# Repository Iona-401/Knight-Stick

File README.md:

# Knight-Stick 🕹️✈️

An open-source, fully 3D-printable flight stick engineered for high-precision simulation, modular assembly, and custom hardware integration.

---

## Overview

Commercial flight simulation gear is often prohibitively expensive or locked into closed ecosystems. **Knight-Stick** bridges that gap by providing a fully customizable, high-performance flight controller that you can manufacture at home using 3D printing and custom electronics.

Designed with a heavy focus on ergonomic feel, mechanical durability, and low-latency input processing, this project brings together mechanical CAD, PCB design, and embedded firmware.

---

## Key Features

* **Ergonomic & Modular CAD:** Designed for additive manufacturing, optimizing print orientation for strength and tactile comfort.
* **Precision Inputs:** Built around low-latency sensor architecture to ensure smooth, dead-zone-free axis tracking and crisp button actuation.
* **Custom Electronics:** Dedicated PCB layout for clean signal routing and reliable peripheral connections.
* **Open Source:** Complete hardware schematics, firmware source code, and STL/CAD files available for modification and community contribution.

---

## Repository Structure

```text
Knight-Stick/
├── cad/          # 3D printable models, mechanical assemblies, and STEP/STL files
├── hardware/     # Schematics, board layouts, and manufacturing files
├── firmware/     # Microcontroller source code and USB HID implementation
└── docs/         # Build guides, wiring diagrams, and assembly instructions

```

---

## Getting Started & Bill of Materials (BOM)

To build your own Knight-Stick, check out the documentation and release files in the respective directories:

1. **Hardware & Electronics:** Review the `hardware/` folder for schematic diagrams and PCB fabrication files.
2. **Mechanical Parts:** Grab the latest printable parts from the `cad/` folder. Ensure you follow recommended print settings for structural rigidity (e.g., adequate infill and wall counts).
3. **Firmware:** Flash the controller using the source code provided in the `firmware/` directory.

---

## Contributing

Contributions, feedback, and forks are always welcome! If you have ideas for improved gimbal geometry, alternative sensor integrations, or firmware enhancements, feel free to open an issue or submit a pull request.

---

## License

This project is open-source. See the repository for license details.

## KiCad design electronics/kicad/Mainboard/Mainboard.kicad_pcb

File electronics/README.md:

# Electronics

This directory contains the complete electronics design for the **Knight Stick**
flight stick, including the schematic, PCB layout, and manufacturing outputs.

The electronics are built around an **ESP32**, providing USB and/or wireless
capabilities suitable for use as a flight simulation controller or general
HID device.

## Contents

- `kicad/`  
  Source design files created with **KiCad**, including:
  - Schematics
  - PCB layout
  - Project configuration files  
  These files represent the authoritative source for the electronics design.

- `gerbers/`  
  Fabrication-ready Gerber and drill files, organized by hardware revision.
  These files can be used directly with PCB manufacturers.

- `bom/`  
  Bill of Materials (BOM) files listing all electronic components required to
  assemble the PCB.

## Manufacturing Notes

- Gerber files are provided for convenience; always refer to the KiCad source
  files if modifications are required.
- Check the BOM and schematic carefully before ordering or assembling boards.

## License

All electronics design files in this directory are licensed under the  
**CERN Open Hardware License v2 – Strongly Reciprocal (CERN-OHL-S)**.

See the root `LICENSE-hardware.txt` file for full license terms.

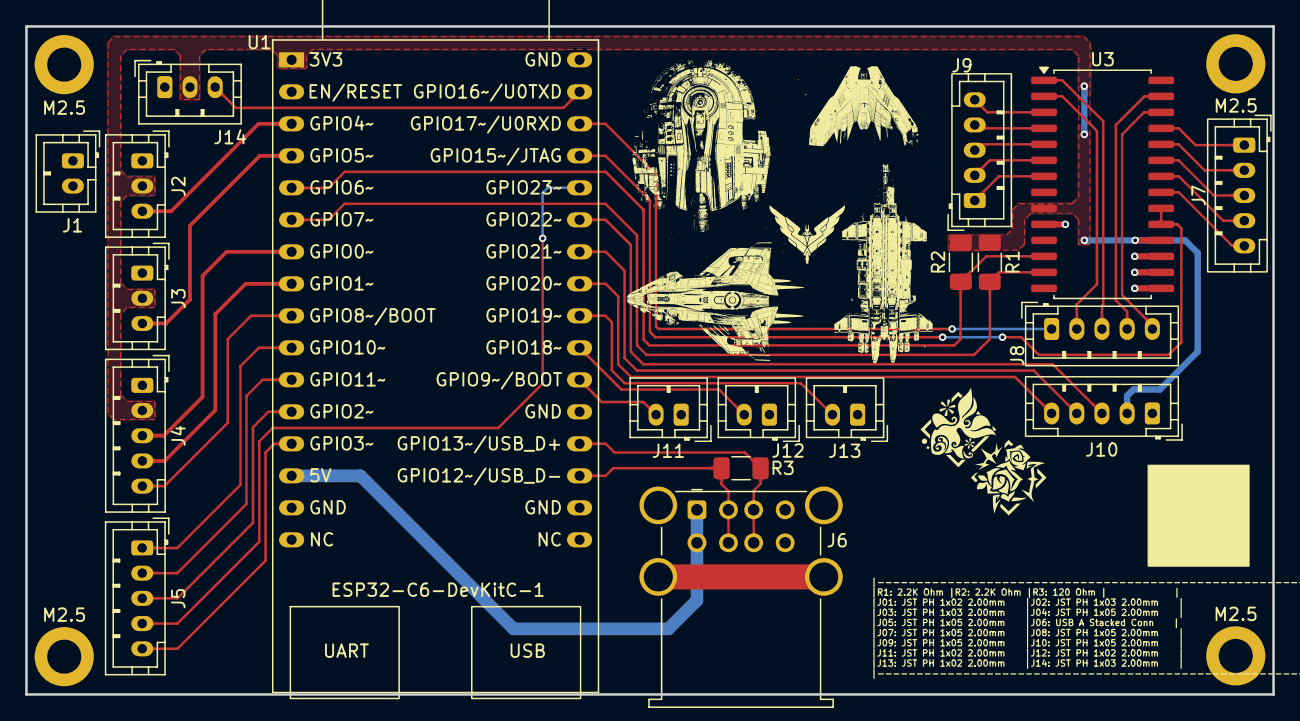
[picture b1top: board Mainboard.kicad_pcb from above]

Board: 2 copper layers, 99.0 x 53.0 mm, 23 parts (0 on the bottom side), 40 nets.

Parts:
J1: GND Pair; JST_PH_B2B-PH-K_1x02_P2.00mm_Vertical
J2: X-Axis Hall; JST_PH_B3B-PH-K_1x03_P2.00mm_Vertical
J3: Y-Axis Hall; JST_PH_B3B-PH-K_1x03_P2.00mm_Vertical
J4, J5, J7, J8, J9, J10: Conn_01x05; JST_PH_B5B-PH-K_1x05_P2.00mm_Vertical
J6: USB_A_Stacked; USB_A_Wuerth_61400826021_Horizontal_Stacked
J11: Box Switch 1; JST_PH_B2B-PH-K_1x02_P2.00mm_Vertical
J12: Box Switch 2; JST_PH_B2B-PH-K_1x02_P2.00mm_Vertical
J13: Bos Switch 3; JST_PH_B2B-PH-K_1x02_P2.00mm_Vertical
J14: LED Strip; JST_PH_B3B-PH-K_1x03_P2.00mm_Vertical
M2.5, M2.5#2, M2.5#3, M2.5#4: MountingHole_2.7mm_M2.5_DIN965_Pad
R1, R2: 2K2; R_1206_3216Metric_Pad1.30x1.75mm_HandSolder
R3: 120; R_1206_3216Metric_Pad1.30x1.75mm_HandSolder
U1: ESP32-C6-DevKitC-1
U3: MCP23017x-x-SO; SOIC-28W_7.5x17.9mm_P1.27mm

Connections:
3V3: J2.2, J3.2, J4.2, J10.2, J14.2, R1.1, R2.1, U1.1 (3V3), U3.9 (V_{DD}), U3.18 (~RESET)
5V: J6.1 (VBUS1), J6.5 (VBUS2), U1.14 (5V)
Base Button: J5.1, U1.10 (GPIO10)
Box Switch 1: J11.2, U1.22 (GPIO9/BOOT)
Box Switch 2: J12.2, U1.23 (GPIO18)
Box Switch 3: J13.2, U1.24 (GPIO19)
CAN-HI: J6.3 (D1+), J6.7 (D2+), R3.1, U1.20 (GPIO13/USB_D+)
CAN-LOW: J6.2 (D1-), J6.6 (D2-), R3.2, U1.19 (GPIO12/USB_D-)
Extra: J14.3, U1.31 (GPIO16/U0TXD)
Face Button: J5.3, U1.12 (GPIO2)
Face Hat Left - Center: J7.5, U3.21 (GPA0)
Face Hat Left - Down: J7.3, U3.23 (GPA2)
Face Hat Left - Left: J7.4, U3.22 (GPA1)
Face Hat Left - Right: J7.2, U3.24 (GPA3)
Face Hat Left - Up: J7.1, U3.25 (GPA4)
Face Hat Right - Center: J8.3, U3.1 (GPB0)
Face Hat Right - Down: J8.1, U1.30 (GPIO17/U0RXD)
Face Hat Right - Left: J8.2, U3.2 (GPB1)
Face Hat Right - Right: J8.4, U3.27 (GPA6)
Face Hat Right - Up: J8.5, U3.26 (GPA5)
GND: J1.1, J1.2, J2.1, J3.1, J4.1, J6.4 (GND1), J6.8 (GND2), J10.1, J11.1, J12.1, J13.1, J14.1, M2.5.1, M2.5#2.1, M2.5#3.1, M2.5#4.1, U1.15 (GND), U1.18 (GND), U1.21 (GND), U1.32 (GND), U3.10 (V_{SS}), U3.15 (A0), U3.16 (A1), U3.17 (A2)
Head Button: J5.2, U1.11 (GPIO11)
INT: U1.29 (GPIO15/JTAG), U3.19 (INTB), U3.20 (INTA)
Joystick Button: J4.5, U1.9 (GPIO8/BOOT)
Joystick X: J4.3, U1.7 (GPIO0)
Joystick Y: J4.4, U1.8 (GPIO1)
Primary Trigger: J5.5, U1.13 (GPIO3)
RE A: J10.4, U1.26 (GPIO21)
RE B: J10.5, U1.25 (GPIO20)
RE Switch: J10.3, U1.27 (GPIO22)
SCK: R2.2, U1.5 (GPIO6), U3.12 (SCK)
SDA: R1.2, U1.6 (GPIO7), U3.13 (SDA)
Secondary Trigger: J5.4, U1.28 (GPIO23)
Thumb Hat - Center: J9.2, U3.6 (GPB5)
Thumb Hat - Down: J9.5, U3.3 (GPB2)
Thumb Hat - Left: J9.1, U3.7 (GPB6)
Thumb Hat - Right: J9.4, U3.4 (GPB3)
Thumb Hat - Up: J9.3, U3.5 (GPB4)
X-Axis: J2.3, U1.3 (GPIO4/MTMS)
Y-Axis: J3.3, U1.4 (GPIO5/MTDI)

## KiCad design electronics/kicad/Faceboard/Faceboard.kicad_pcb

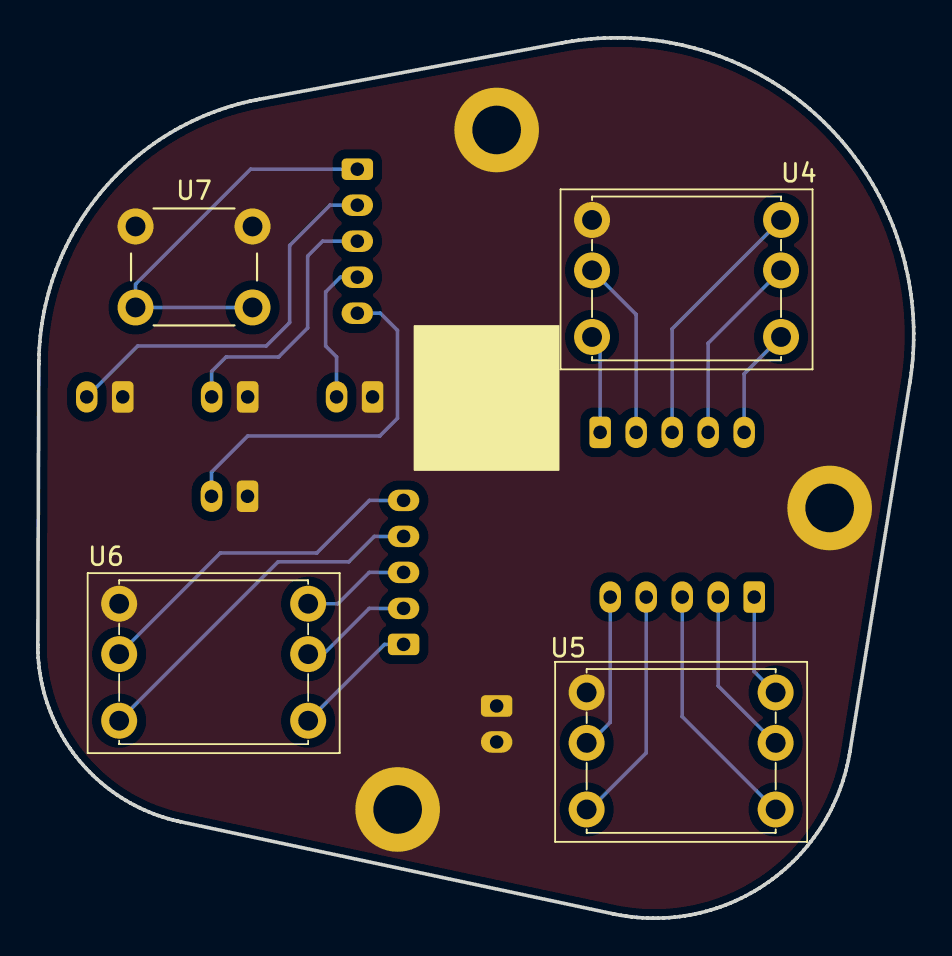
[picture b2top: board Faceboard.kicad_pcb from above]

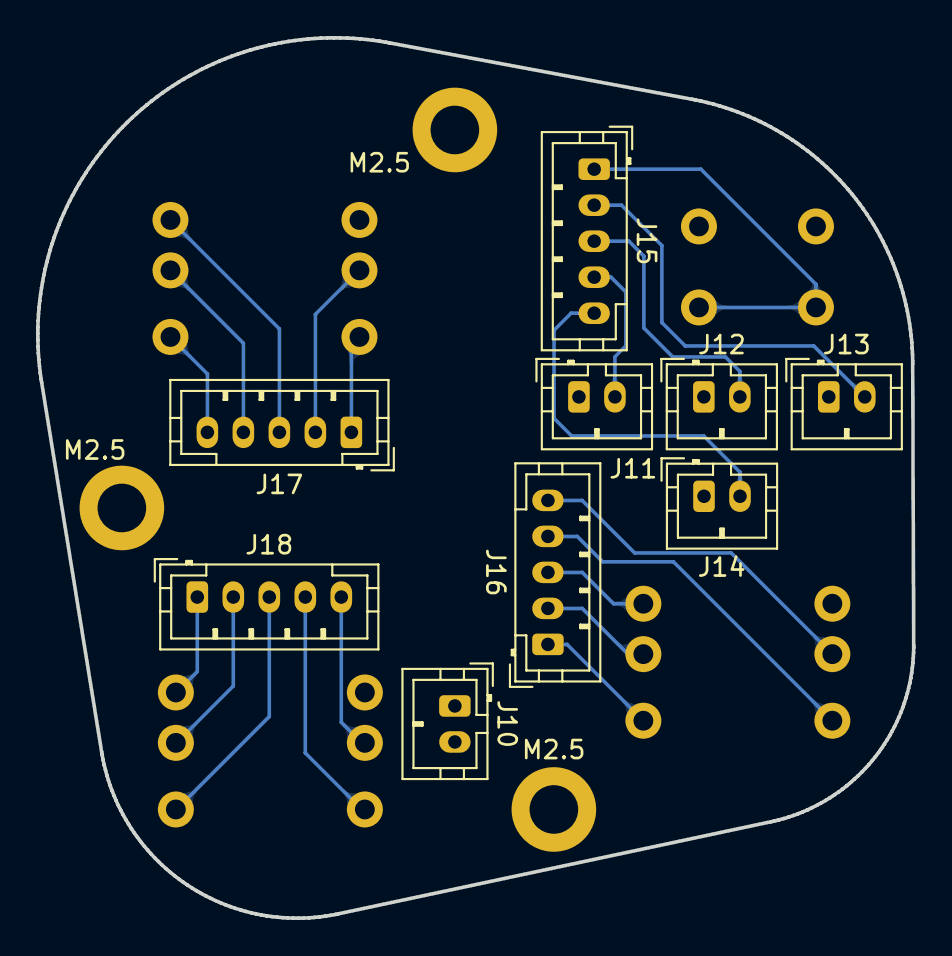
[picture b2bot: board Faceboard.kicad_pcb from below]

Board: 2 copper layers, 48.7 x 48.9 mm, 16 parts (12 on the bottom side), 21 nets.

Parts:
J10: Gnd; JST_PH_B2B-PH-K_1x02_P2.00mm_Vertical
J11: Primary Trigger 1; JST_PH_B2B-PH-K_1x02_P2.00mm_Vertical
J12: Secondary Trigger; JST_PH_B2B-PH-K_1x02_P2.00mm_Vertical
J13: Head Button; JST_PH_B2B-PH-K_1x02_P2.00mm_Vertical
J14: Base Button; JST_PH_B2B-PH-K_1x02_P2.00mm_Vertical
J15, J16, J17, J18: Conn_01x05; JST_PH_B5B-PH-K_1x05_P2.00mm_Vertical
M2.5, M2.5#2, M2.5#3: MountingHole_2.7mm_M2.5_DIN965_Pad
U4: Face Hat Top; 5-Way_Tact_Swt_6-pin
U5: Face Hat Right; 5-Way_Tactile_Swt_6-pin
U6: Face Hat Left; 5-Way_Tactile_Swt_6-pin
U7: Face Button; SW_PUSH_6mm_H5mm

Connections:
Base Button: J14.2, J15.5
Face Button: J15.1, U7.2
Face Hat Left - Center: J18.4, U6.3 (Center)
Face Hat Left - Down: J18.3, U6.6 (Down)
Face Hat Left - Left: J18.5, U6.2 (Left)
Face Hat Left - Right: J18.2, U6.5 (Right)
Face Hat Left - Up: J18.1, U6.4 (Up)
Face Hat Right - Center: J16.4, U5.3 (Center)
Face Hat Right - Down: J16.1, U5.6 (Down)
Face Hat Right - Left: J16.5, U5.2 (Left)
Face Hat Right - Right: J16.2, U5.5 (Right)
Face Hat Right - Up: J16.3, U5.4 (Up)
GND: J10.1, J10.2, J11.1, J12.1, J13.1, J14.1, M2.5.1, M2.5#2.1, M2.5#3.1, U4.1 (GND), U5.1 (GND), U6.1 (GND), U7.1
Head Button: J13.2, J15.2
Primary Trigger 1: J11.2, J15.4
Secondary Trigger: J12.2, J15.3
Thumb Hat - Center: J17.1, U4.3 (Center)
Thumb Hat - Down: J17.5, U4.6 (Down)
Thumb Hat - Left: J17.2, U4.2 (Left)
Thumb Hat - Right: J17.4, U4.5 (Right)
Thumb Hat - Up: J17.3, U4.4 (Up)

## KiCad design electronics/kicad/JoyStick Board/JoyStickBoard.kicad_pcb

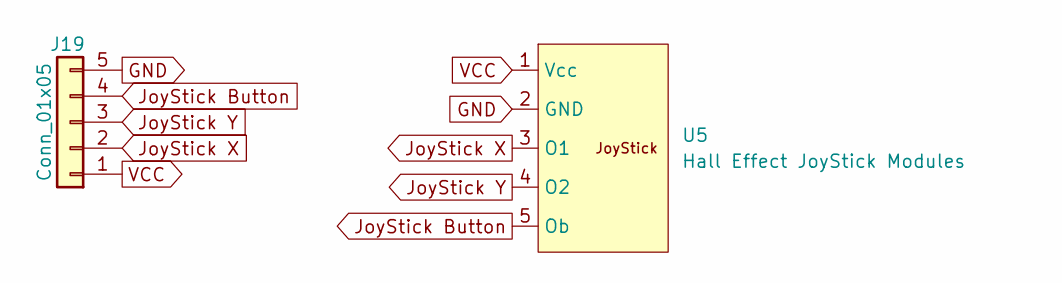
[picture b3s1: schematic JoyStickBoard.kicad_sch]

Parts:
J19: Conn_01x05; JST_PH_B5B-PH-K_1x05_P2.00mm_Vertical
U5: Hall Effect JoyStick Modules; Generic 2 axis Joystick with button

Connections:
GND: J19.5, U5.2 (GND)
JoyStick Button: J19.4, U5.5 (Ob)
JoyStick X: J19.2, U5.3 (O1)
JoyStick Y: J19.3, U5.4 (O2)
VCC: J19.1, U5.1 (Vcc)

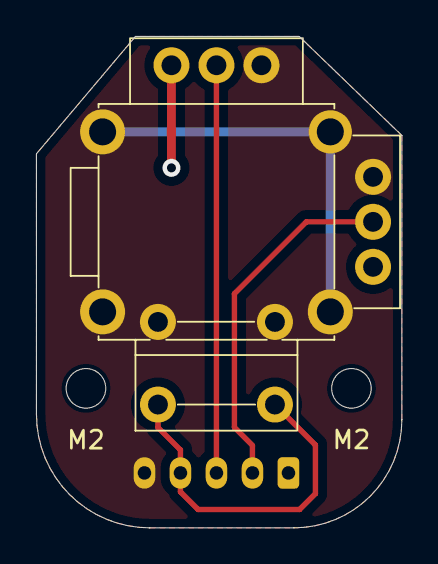
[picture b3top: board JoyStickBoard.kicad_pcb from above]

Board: 2 copper layers, 20.3 x 27.3 mm, 4 parts (1 on the bottom side), 5 nets.

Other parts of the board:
M2, M2#2: MountingHole_2.2mm_M2_DIN965_Pad

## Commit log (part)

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2026-03-21 Add CERN Open Hardware Licence Version 2 document
2026-03-21 Add MIT License to the project
2026-03-21 changed license to license-software
2026-03-21 Add README files for electronics and firmware directories
2026-03-21 Added 3D Print README and STEP Files
    Added all the STEP Files for the Flight stick and modified the readme to reflect the print list.
    Added a base print profile for Orca Slicer.
2026-03-23 Added all KiCad schematics. PCBs, projects files, and all related gerbers
2026-03-23 Updates gerbers to include QR Code patch for JLCPCB
2026-03-23 Enhance README with detailed electronics design info
    Expanded README to include details about the Knight Stick flight stick and its components.
2026-03-23 Revise README for Knight Stick mechanical design
    Updated README to include detailed descriptions of mechanical design files and 3D printing notes.
2026-03-23 Mark firmware as work in progress
    Added a note indicating that the firmware is a work in progress.
2026-03-24 Updated Print Files to current version
2026-04-13 Updated PCB with New Silkscreen
